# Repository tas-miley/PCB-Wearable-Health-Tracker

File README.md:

# PCB-Wearable-Health-Tracker
PCB design to run the firmware for the Wearable Health Tracker project. The goal of this PCB is to support SPO2 and IMU sensors, BLE communication, and LiPo battery power/charging. It's also designed to be ~1 inch x 1 inch to support wrist wearability.

Completed:
- Component selection (Max30102, LSM6DSOX, nRF52833, voltage regulators)
- Battery Selection (LiPo 150mAh)
- Connector choice (USB-C for charging, battery connector, Tag Connect for programming)
- Initial 2 layer trace layout
- 

Todo:
- Move from 2 layer to 4 layer board, with GND and PWR planes

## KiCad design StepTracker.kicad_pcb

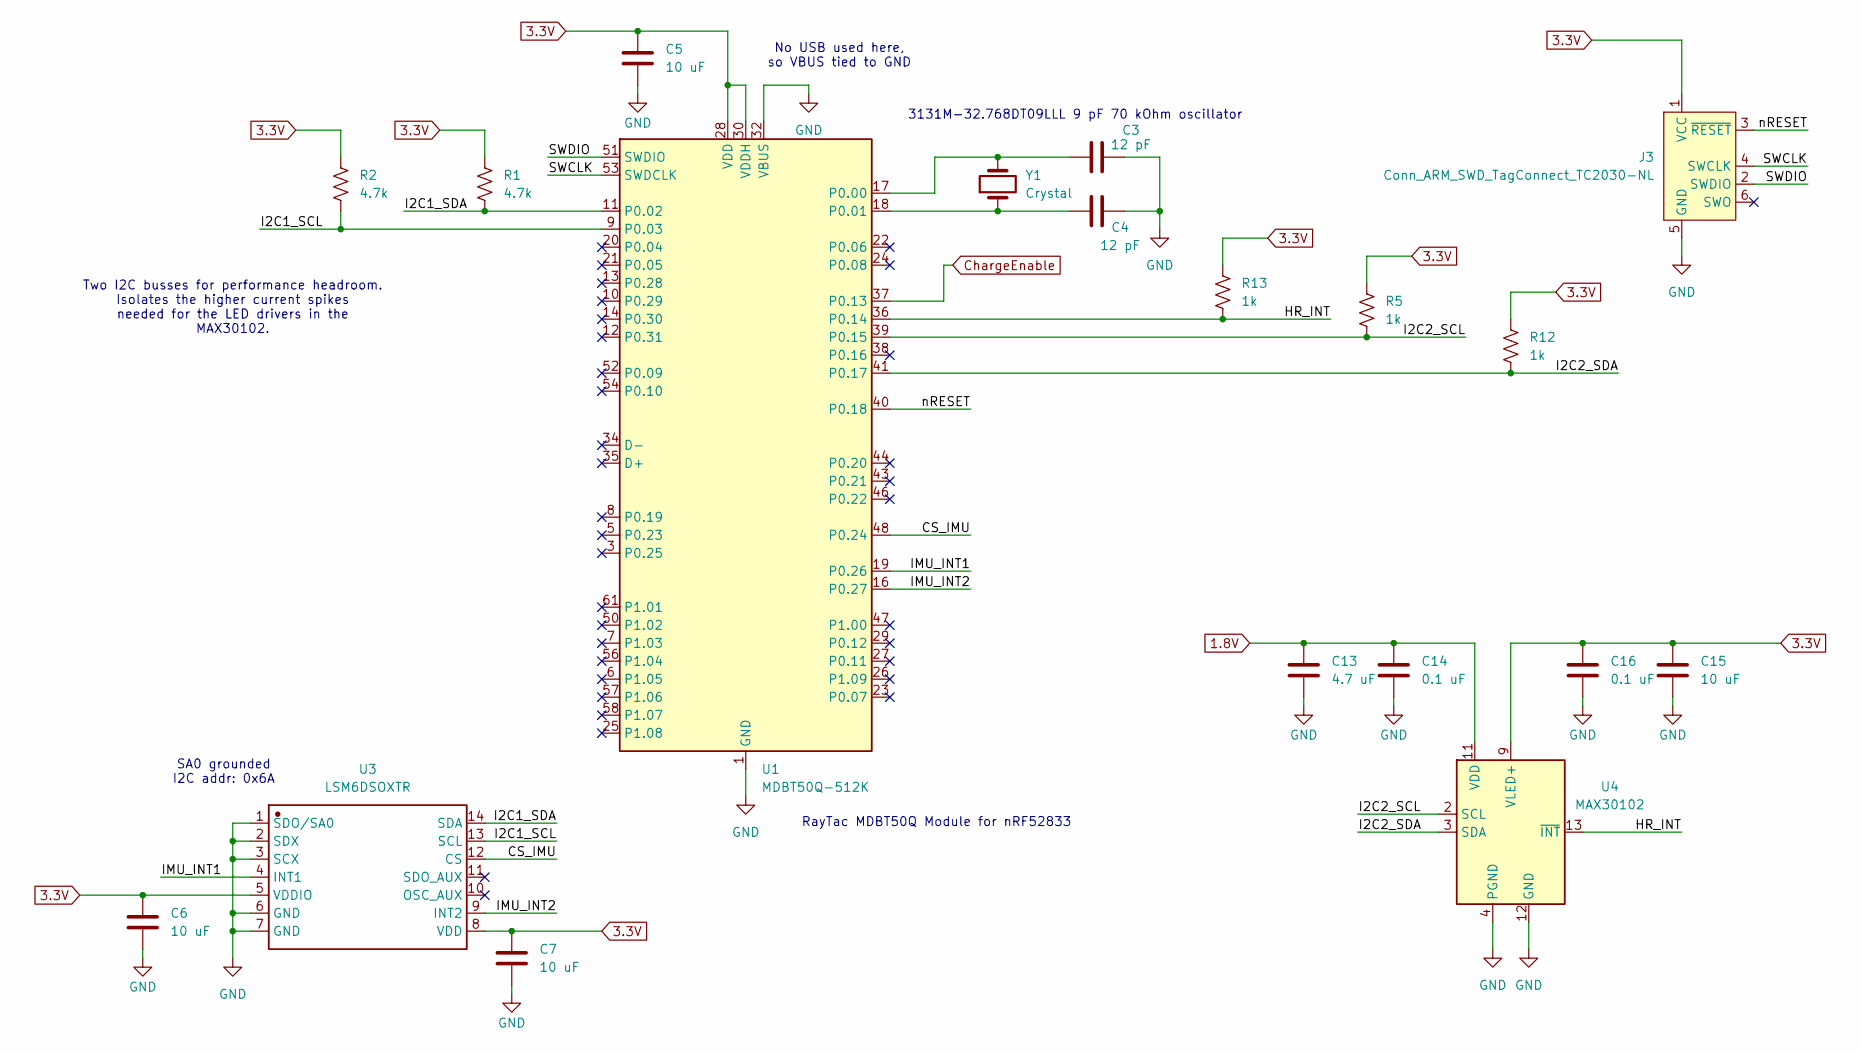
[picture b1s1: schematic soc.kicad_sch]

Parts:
C3, C4: 12 pF; C_0402
C5, C6, C7, C15: 10 uF; C_0402
C13: 4.7 uF; C_0402
C14, C16: 0.1 uF; C_0402
J3: Conn_ARM_SWD_TagConnect_TC2030-NL; Tag-Connect_TC2030-IDC-NL_2x03_P1.27mm_Vertical
R1, R2: 4.7k; R_0402
R5, R12, R13: 1k; R_0402
U1: MDBT50Q-512K; Raytac_MDBT50Q
U3: LSM6DSOXTR; LSM6DSOX; Manufacturer Part LSM6DSOXTR
U4: MAX30102; Maxim_OLGA-14_3.3x5.6mm_P0.8mm
Y1: Crystal; Crystal_3131M

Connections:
1.8V: C13.1, C14.1, U4.11 (VDD); also elsewhere on the board
3.3V: C5.1, C6.1, C7.1, C15.1, C16.2, J3.1 (VCC), R1.1, R2.1, R5.1, R12.1, R13.1, U1.28 (VDD), U1.30 (VDDH), U3.5 (VDDIO), U3.8 (VDD), U4.9 (VLED+), U4.10 (VLED+); also elsewhere on the board
/SOC/CS_IMU: U1.48 (P0.24), U3.12 (CS)
/SOC/HR_INT: R13.2, U1.36 (P0.14), U4.13 (~INT)
/SOC/I2C1_SCL: R2.2, U1.9 (P0.03), U3.13 (SCL)
/SOC/I2C1_SDA: R1.2, U1.11 (P0.02), U3.14 (SDA)
/SOC/I2C2_SCL: R5.2, U1.39 (P0.15), U4.2 (SCL)
/SOC/I2C2_SDA: R12.2, U1.41 (P0.17), U4.3 (SDA)
/SOC/IMU_INT1: U1.19 (P0.26), U3.4 (INT1)
/SOC/IMU_INT2: U1.16 (P0.27), U3.9 (INT2)
/SOC/SWCLK: J3.4 (SWCLK), U1.53 (SWDCLK)
/SOC/SWDIO: J3.2 (SWDIO), U1.51 (SWDIO)
/SOC/nRESET: J3.3 (~RESET), U1.40 (P0.18)
ChargeEnable: U1.37 (P0.13); also elsewhere on the board
GND: C3.2, C4.2, C5.2, C6.2, C7.2, C13.2, C14.2, C15.2, C16.1, J3.5 (GND), U1.1 (GND), U1.2 (GND), U1.15 (GND), U1.32 (VBUS), U1.33 (GND), U1.55 (GND), U3.1 (SDO/SA0), U3.2 (SDX), U3.3 (SCX), U3.6 (GND), U3.7 (GND), U4.4 (PGND), U4.12 (GND); also elsewhere on the board
unnamed: C3.1, U1.17 (P0.00), Y1.2
unnamed: C4.1, U1.18 (P0.01), Y1.1

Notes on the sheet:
3131M-32.768DT09LLL 9 pF 70 kOhm oscillator
Two I2C busses for performance headroom. Isolates the higher current spikes needed for the LED drivers in the MAX30102.
RayTac MDBT50Q Module for nRF52833
SA0 grounded I2C addr: 0x6A
No USB used here, so VBUS tied to GND

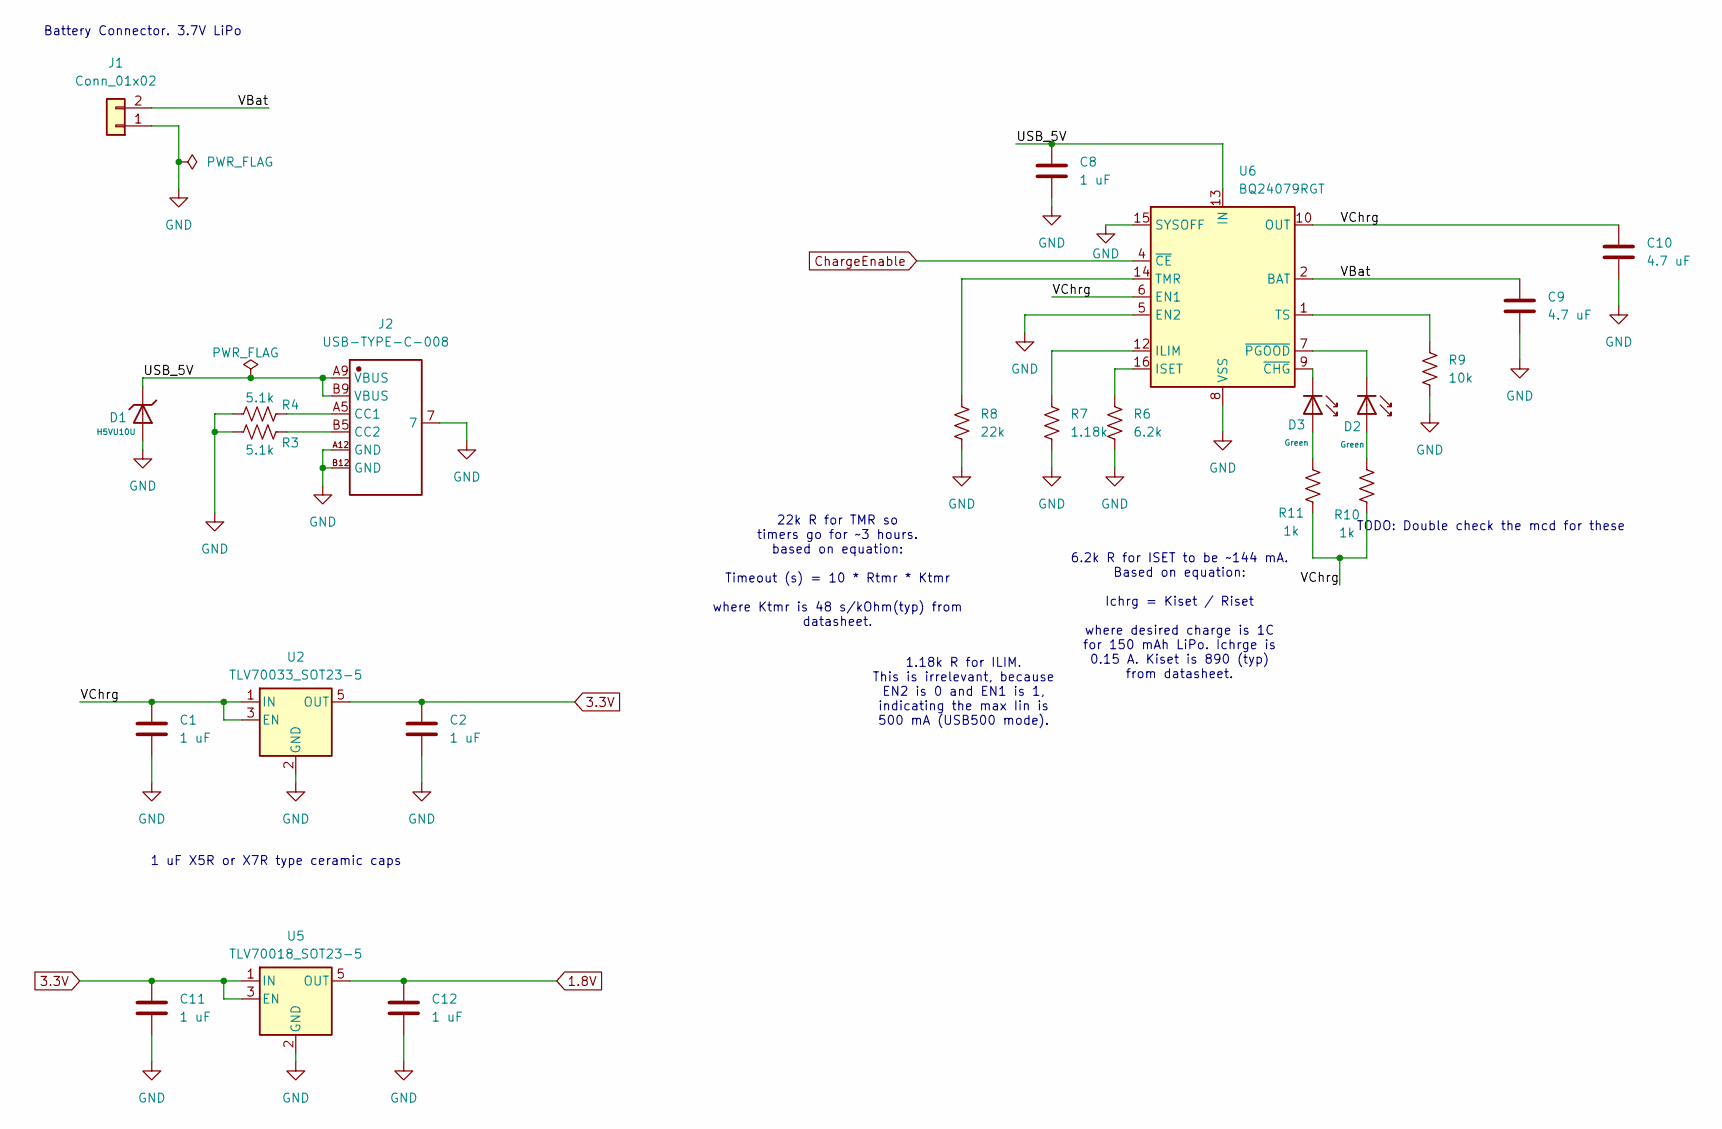
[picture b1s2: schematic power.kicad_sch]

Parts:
C1, C2, C8, C11, C12: 1 uF; C_0402
C9, C10: 4.7 uF; C_0402
D1: H5VU10U; D_DFN1006-2L; Breakdown Voltage 9V; Part H5VU10U; LCSC C22395519
D2, D3: Green; D_0805; Part KT-0805G; LCSC C2297
J1: Conn_01x02; JST_EH_S2B-EH_1x02_P2.50mm_Horizontal
J2: USB-TYPE-C-008; USB-C-SMD_TYPE-602-T3; Manufacturer Part USB-TYPE-C-008
R3, R4: 5.1k; R_0402
R6: 6.2k; R_0402
R7: 1.18k; R_0402
R8: 22k; R_0402
R9: 10k; R_0402
R10, R11: 1k; R_0402
U2: TLV70033_SOT23-5; SOT-23-5
U5: TLV70018_SOT23-5; SOT-23-5
U6: BQ24079RGT; VQFN-16-1EP_3x3mm_P0.5mm_EP1.6x1.6mm

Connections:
1.8V: C12.1, U5.5 (OUT); also elsewhere on the board
3.3V: C2.1, C11.1, U2.5 (OUT), U5.1 (IN), U5.3 (EN); also elsewhere on the board
/Power/USB_5V: C8.1, D1.1, J2.A9 (VBUS), J2.B9 (VBUS), U6.13 (IN)
/Power/VBat: C9.1, J1.2, U6.2 (BAT), U6.3 (BAT)
/Power/VChrg: C1.1, C10.1, R10.2, R11.2, U2.1 (IN), U2.3 (EN), U6.6 (EN1), U6.10 (OUT), U6.11 (OUT)
ChargeEnable: U6.4 (~CE); also elsewhere on the board
GND: C1.2, C2.2, C8.2, C9.2, C10.2, C11.2, C12.2, D1.2, J1.1, J2.7, J2.A12 (GND), J2.B12 (GND), R3.2, R4.2, R6.2, R7.2, R8.2, R9.2, U2.2 (GND), U5.2 (GND), U6.5 (EN2), U6.8 (VSS), U6.15 (SYSOFF), U6.17 (VSS); also elsewhere on the board
unnamed: D2.2, R10.1
unnamed: D3.2, R11.1
unnamed: J2.A5 (CC1), R4.1
unnamed: J2.B5 (CC2), R3.1
unnamed: R7.1, U6.12 (ILIM)
unnamed: R6.1, U6.16 (ISET)
unnamed: R8.1, U6.14 (TMR)
unnamed: R9.1, U6.1 (TS)
unnamed: D3.1, U6.9 (~CHG)
unnamed: D2.1, U6.7 (~PGOOD)

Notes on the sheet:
1.18k R for ILIM. This is irrelevant, because EN2 is 0 and EN1 is 1, indicating the max Iin is 500 mA (USB500 mode).
TODO: Double check the mcd for these
1 uF X5R or X7R type ceramic caps
22k R for TMR so timers go for ~3 hours. based on equation: Timeout (s) = 10 * Rtmr * Ktmr where Ktmr is 48 s/kOhm(typ) from datasheet.
6.2k R for ISET to be ~144 mA. Based on equation: Ichrg = Kiset / Riset where desired charge is 1C for 150 mAh LiPo. Ichrge is 0.15 A. Kiset is 890 (typ) from datasheet.
Battery Connector. 3.7V LiPo

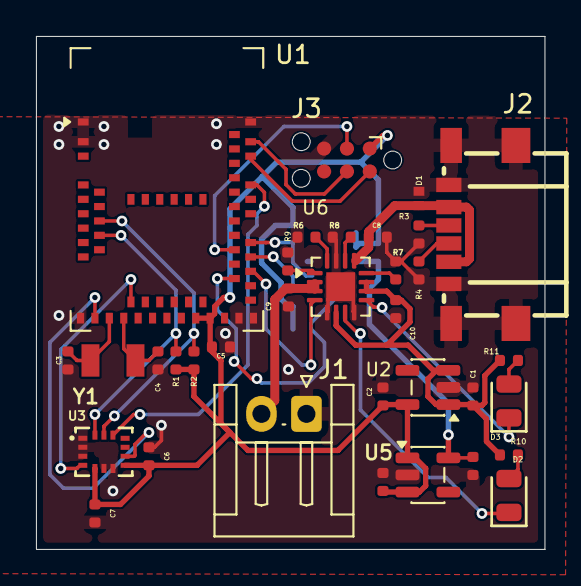
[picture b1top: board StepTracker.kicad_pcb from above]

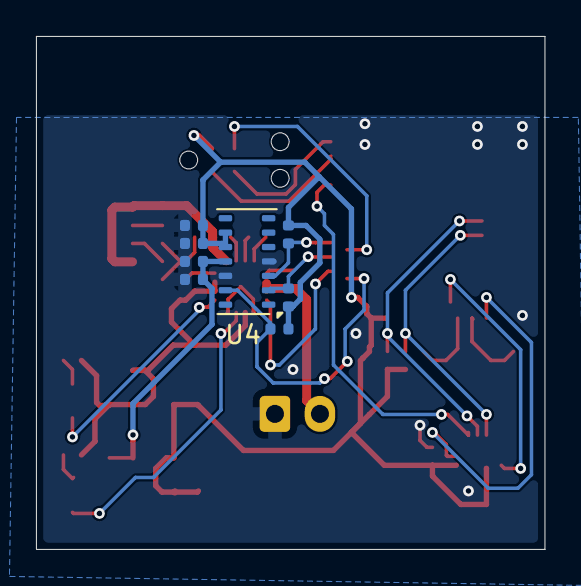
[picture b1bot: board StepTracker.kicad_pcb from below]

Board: 2 copper layers, 28.2 x 28.5 mm, 42 parts (8 on the bottom side), 30 nets.

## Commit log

2026-04-21 initial tracking of schematic and PCB layout
2026-04-22 update to include footprints from project specific lib
